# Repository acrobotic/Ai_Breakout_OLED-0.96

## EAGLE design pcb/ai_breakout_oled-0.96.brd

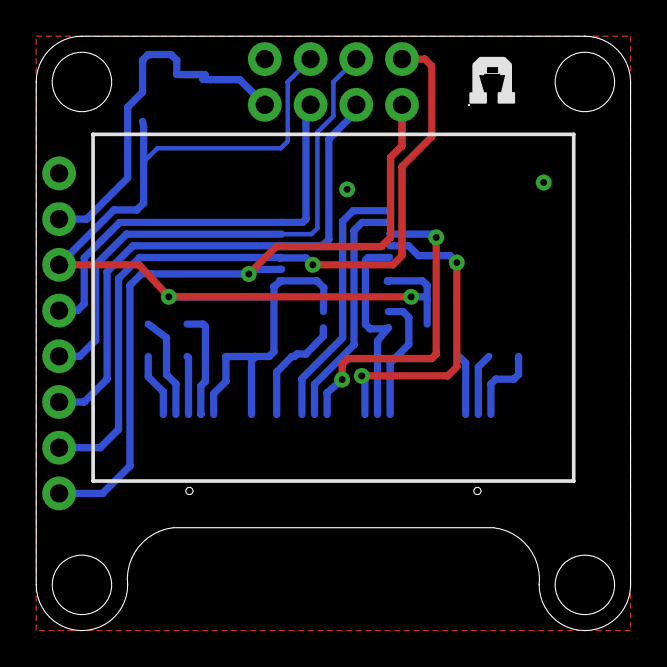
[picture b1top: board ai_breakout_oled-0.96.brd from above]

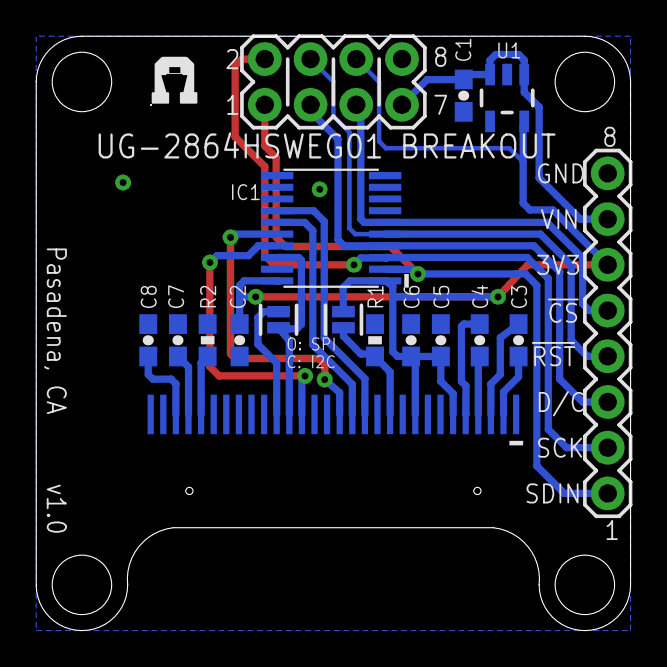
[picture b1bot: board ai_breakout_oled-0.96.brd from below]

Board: 2 copper layers, 33.0 x 33.0 mm, 23 parts (17 on the bottom side), 22 nets.

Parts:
C1, C2, C8: 10uF; CAP-0603
C3, C4, C5, C6, C7: 2.2uF; CAP-0603
IC1: 74HCT245MTC; SSOP20
J1: 2X04
J2: 1X08
JS1, JS2: 1X02-SJ-NO
M1, M2, M3, M4: STAND-OFF
OLED1: UG-2864HSWEG01; UG-2864HSWEG01_0.96_WRAP
R1: 10K; RES-0603
R2: 390K; RES-0603
U1: MIC5205-3.3; SOT23-5
U$15, U$16: AI-LOGOXS; AI-LOGO-XS

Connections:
3V3: C2.2, C5.2, C6.2, IC1.1, IC1.20, J1.6, J2.6, JS2.2, OLED1.6, OLED1.9, U1.5
CS_3V3: IC1.14, OLED1.13
CS_IN: IC1.6, J1.5, J2.5
D0/SCLK/SCK_3V3: IC1.17, OLED1.18
D0/SCLK/SCK_IN: IC1.3, J1.2, J2.2
D1/MOSI/SDA1_3V3: IC1.18, JS1.1, OLED1.19
D1/MOSI/SDA1_IN: IC1.2, J1.1, J2.1
DC/SA0_3V3: IC1.16, OLED1.15
DC/SA0_IN: IC1.4, J1.3, J2.3
GND: C1.1, C2.1, C5.1, C6.1, C7.1, C8.1, IC1.10, IC1.19, J1.8, J2.8, OLED1.1, OLED1.8, OLED1.10, OLED1.12, OLED1.16, OLED1.17, OLED1.21, OLED1.22, OLED1.23, OLED1.24, OLED1.25, OLED1.29, OLED1.30, R1.1, R2.1, U1.2
I2C_EN: JS2.1, OLED1.11, R1.2
unnamed: OLED1.26, R2.2
unnamed: C3.2, OLED1.2
unnamed: C3.1, OLED1.3
unnamed: C4.2, OLED1.4
unnamed: C4.1, OLED1.5
unnamed: JS1.2, OLED1.20
unnamed: C8.2, OLED1.28
unnamed: C7.2, OLED1.27
RST_3V3: IC1.15, OLED1.14
RST_IN: IC1.5, J1.4, J2.4
VIN: C1.2, J1.7, J2.7, U1.1, U1.3

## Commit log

2014-10-31 routing done
2014-10-31 ready for fabrication
2014-10-31 ready for manufacturing
2014-11-03 renaming step 1
2014-11-03 renaming step 2
2014-11-20 Adding BOM. Minor silkscreen changes
